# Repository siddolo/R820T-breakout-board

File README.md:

# Rafael Micro R820 Breakout Board

A simple radio front-end for rapid prototyping purposes. It implements the minimum circuit needed by the R820T chip, exposing the I2C bus, the IF output, and the ACG control of the tuner.

R820T KiCad library: https://github.com/siddolo/kicad-library

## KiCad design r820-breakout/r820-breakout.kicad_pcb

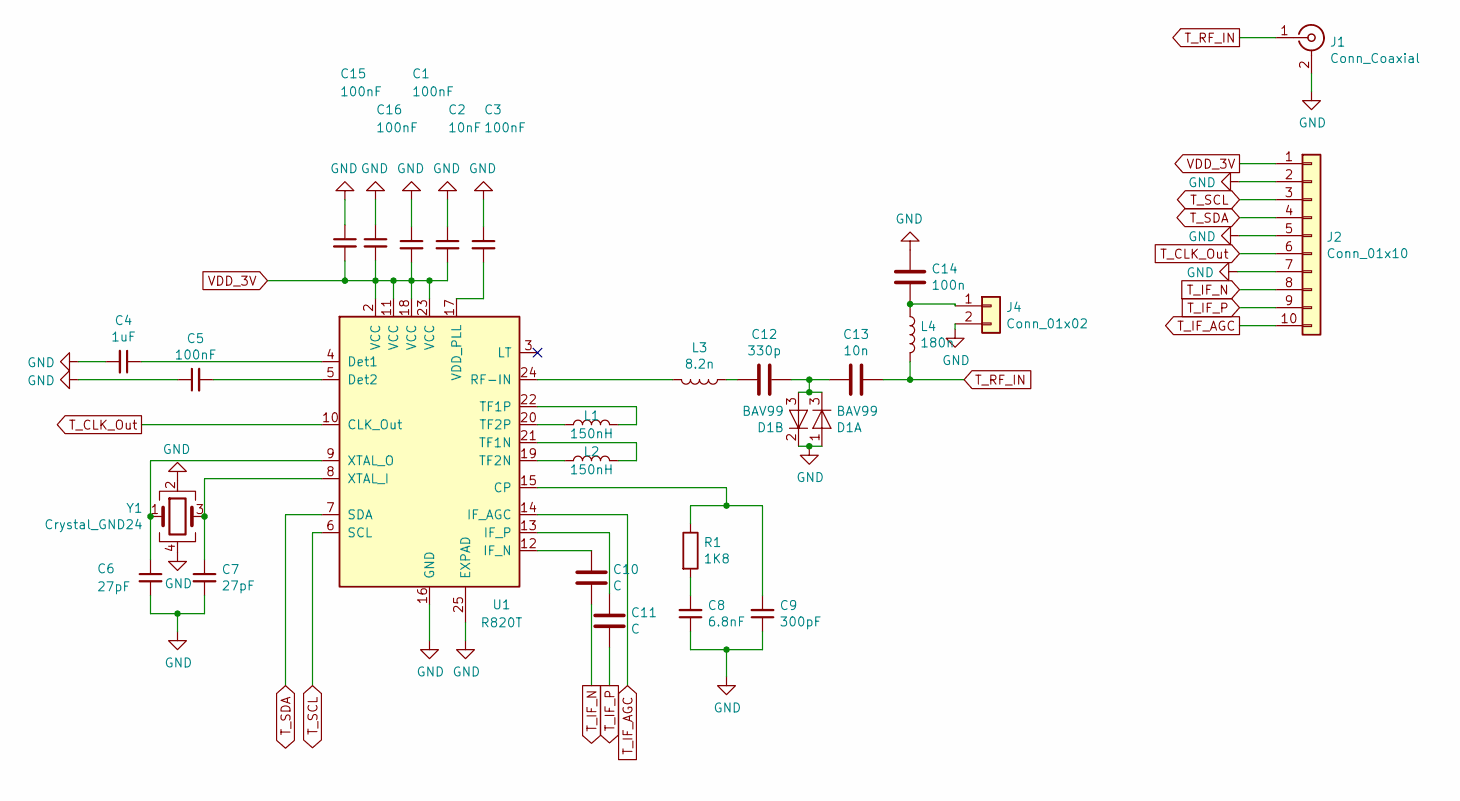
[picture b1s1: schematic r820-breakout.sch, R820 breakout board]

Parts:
C1, C3, C5, C15, C16: 100nF; C_0402_1005Metric
C2: 10nF; C_0402_1005Metric
C4: 1uF; C_0603_1608Metric
C6, C7: 27pF; C_0603_1608Metric
C8: 6.8nF; C_0603_1608Metric
C9: 300pF; C_0603_1608Metric
C10, C11: C; C_0402_1005Metric
C12: 330p; C_0603_1608Metric
C13: 10n; C_0603_1608Metric
C14: 100n; C_0603_1608Metric
D1: BAV99; SOT-23
J1: Conn_Coaxial; Molex_SMA_Jack_Edge_Mount
J2: Conn_01x10; PinHeader_1x10_P2.54mm_Vertical
J4: Conn_01x02; PinHeader_1x02_P2.54mm_Vertical
L1, L2: 150nH; L_0603_1608Metric
L3: 8.2n; L_0603_1608Metric
L4: 180n; L_0603_1608Metric
R1: 1K8; R_0603_1608Metric
U1: R820T; QFN-24-1EP_4x4mm_P0.5mm_EP2.7x2.7mm_ThermalVias
Y1: Crystal_GND24; Crystal_SMD_TXC_7M-4Pin_3.2x2.5mm

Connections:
GND: C1.1, C2.1, C3.1, C4.2, C5.1, C6.2, C7.2, C8.1, C9.1, C14.1, C15.1, C16.1, D1.1 (A), D1.2 (K), J1.2 (Ext), J2.2, J2.5, J2.7, J4.2, U1.16 (GND), U1.25 (EXPAD), Y1.2, Y1.4
unnamed: C3.2, U1.17 (VDD_PLL)
unnamed: C4.1, U1.4 (Det1)
unnamed: C5.2, U1.5 (Det2)
unnamed: C6.1, U1.9 (XTAL_O), Y1.1
unnamed: C7.1, U1.8 (XTAL_I), Y1.3
unnamed: C8.2, R1.2
unnamed: C9.2, R1.1, U1.15 (CP)
unnamed: C10.1, U1.12 (IF_N)
unnamed: C11.1, U1.13 (IF_P)
unnamed: C12.1, C13.2, D1.3 (K)
unnamed: C12.2, L3.1
unnamed: C14.2, J4.1, L4.1
unnamed: L1.1, U1.20 (TF2P)
unnamed: L1.2, U1.22 (TF1P)
unnamed: L2.1, U1.19 (TF2N)
unnamed: L2.2, U1.21 (TF1N)
unnamed: L3.2, U1.24 (RF-IN)
T_CLK_Out: J2.6, U1.10 (CLK_Out)
T_IF_AGC: J2.10, U1.14 (IF_AGC)
T_IF_N: C10.2, J2.8
T_IF_P: C11.2, J2.9
T_RF_IN: C13.1, J1.1 (In), L4.2
T_SCL: J2.3, U1.6 (SCL)
T_SDA: J2.4, U1.7 (SDA)
VDD_3V: C1.2, C2.2, C15.2, C16.2, J2.1, U1.2 (VCC), U1.11 (VCC), U1.18 (VCC), U1.23 (VCC)

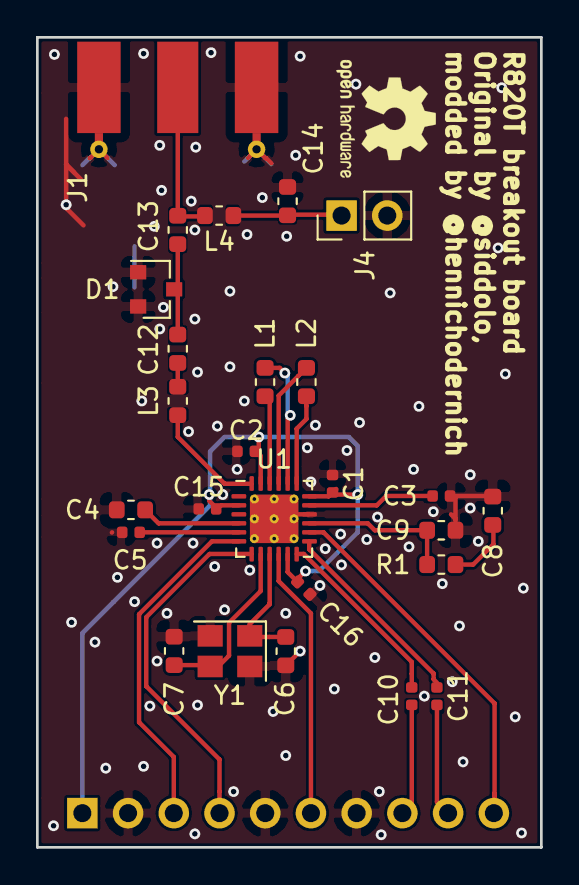
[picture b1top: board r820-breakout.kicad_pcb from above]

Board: 2 copper layers, 28.0 x 45.0 mm, 27 parts (1 on the bottom side), 26 nets.

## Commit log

2019-05-19 R820T breakout board
2019-05-19 README
2019-05-20 title
2019-05-20 Create LICENSE
2019-05-20 add dimension
2019-05-20 added KiCad library reference
2019-05-20 added description to readme
2019-05-21 Heavily reworked.
2019-05-23 footprint fix, added OSH logo, removed big via under rt820t
2019-05-23 add hennichodernich to authors
2019-05-23 Fix F.Cu fill zone clearance
2019-05-23 fix some value
2023-12-22 Ko-fi
